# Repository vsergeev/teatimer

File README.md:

# teatimer

A simple kitchen timer implemented in digital logic on a Lattice MachXO2 CPLD.

(It's brighter in person.)

## Details

* Features
    * Large 7-segment display
    * Count-down/count-up timer
    * Alarm and silent modes
    * AAA battery powered
* Limitations
    * 10 hour battery life
* ICs
    * Lattice MachXO2-256 CPLD
    * SG-3030JC 32.768 kHz Oscillator
    * TLV61225 Boost Converter 1.5V -> 3.3V
* Dimensions of 80mm x 49mm
* Power consumption of ~100mA @ 1.5V (mostly from LEDs)

## Project Structure

* [`README.md`](README.md) - this README
* [`teatimer.v`](teatimer.v) - Verilog source
* [`teatimer_tb.v`](teatimer_tb.v) - Verilog test bench
* [`Makefile`](Makefile) - Makefile for simulation
* [`hw/`](hw/) - Schematic and layout
    * `teatimer.sch` - Eagle schematic
    * `teatimer.brd` - Eagle layout
    * [`teatimer-sch.png`](hw/teatimer-sch.png) - Schematic image
    * [`teatimer-brd.png`](hw/teatimer-brd.png) - Layout image
    * [`gerbers/`](hw/gerbers/) - Gerbers
* [`diamond/`](diamond/) - Lattice Diamond project
    * `teatimer.ldf` - Project file
    * `teatimer.v` - Symlinked Verilog source
    * [`teatimer.lpf`](diamond/teatimer.lpf) - Constraints
    * [`teatimer.jed`](diamond/teatimer.jed) - JEDEC bitstream
* [`misc/`](misc/) - Miscellaneous scripts

## Design Summary

The design uses 67 bits of state, 91% of the LUTs for logic, and all of the
I/O.

```
Number of registers:     67 out of   322 (21%)
   PFU registers:           63 out of   256 (25%)
   PIO registers:            4 out of    66 (6%)
Number of SLICEs:       117 out of   128 (91%)
   SLICEs as Logic/ROM:    117 out of   128 (91%)
   SLICEs as RAM:            0 out of    96 (0%)
   SLICEs as Carry:         27 out of   128 (21%)
Number of LUT4s:        232 out of   256 (91%)
   Number used as logic LUTs:        178
   Number used as distributed RAM:     0
   Number used as ripple logic:       54
   Number used as shift registers:     0
Number of PIO sites used: 18 + 4(JTAG) out of 22 (100%)
Number of block RAMs:  0 out of 0
Number of GSRs:  1 out of 1 (100%)
```

## Datasheets

* U1, Lattice MachXO2 CPLD, LCMXO2-256HC-4SG32C - [family datasheet](http://www.latticesemi.com/~/media/LatticeSemi/Documents/DataSheets/MachXO23/MachXO2FamilyDataSheet.pdf)
* U2, 32.768 kHz Oscillator, SG-3030JC32.7680KB:ROHS - [datasheet](https://support.epson.biz/td/api/doc_check.php?dl=brief_SG-3040JC)
* U3, Boost Converter, TLV61225DCKR - [datasheet](http://www.ti.com/lit/ds/symlink/tlv61225.pdf)
* DISP1, 7-segment Display, HDSP-B03E - [datasheet](https://docs.broadcom.com/docs/AV02-0568EN)
* SP1, 4kHz Buzzer, PKM13EPYH4000-A0 - [datasheet](http://search.murata.co.jp/Ceramy/image/img/w_hinm/S0040E.pdf)

## Schematic

## Layout

## Bill of Materials

| Qty | Part                      | Refdes             | Digi-key Part Number       | Total Price |
|:----|:--------------------------|:-------------------|:---------------------------|:------------|
| 1   | Lattice MachXO2-256 CPLD  | U1                 | 220-2636-ND                | 2.830       |
| 1   | Oscillator 32.768kHz      | U2                 | SG-3030JC32.7680KB:ROHS-ND | 1.398       |
| 1   | TLV61225 Boost Converter  | U3                 | 296-36756-1-ND             | 0.775       |
| 1   | NPN BJT (Buzzer Driver)   | Q1                 | BC817-40LT1GOSCT-ND        | 0.103       |
| 1   | PMOS FET (Polarity Prot.) | Q2                 | SI2365EDS-T1-GE3CT-ND      | 0.297       |
| 4   | Tactile Switch (Buttons)  | SW1-SW4            | CKN9085CT-ND               | 0.776       |
| 1   | Slide Switch (Power)      | SW5                | CKN9558-ND                 | 0.648       |
| 1   | 7-segment LED Display     | DISP1              | 516-2745-ND                | 2.821       |
| 1   | Buzzer 4kHz               | SP1                | 490-4698-ND                | 0.499       |
| 1   | Battery Connector AAA     | J1                 | 36-2466-ND                 | 0.928       |
| 1   | SMD Header 1x6            | JP1                | 952-3235-ND                | 0.711       |
| 1   | Inductor 4.7uH            | L1                 | 1276-6213-1-ND             | 0.153       |
| 1   | Capacitor 47uF 0603       | C1                 | 311-1897-1-ND              | 0.322       |
| 2   | Capacitor 10uF 0603       | C2,C3              | 587-3258-1-ND              | 0.238       |
| 10  | Capacitor 0.1uF 0603      | C4-C13             | 1276-1005-1-ND             | 0.073       |
| 6   | Resistor 10K 0603         | R1,R3,R5,R7,R9,R19 | 311-10KGRCT-ND             | 0.033       |
| 4   | Resistor 100K 0603        | R2,R4,R6,R8        | 311-100KGRCT-ND            | 0.029       |
| 1   | Resistor 1K 0603          | R10                | 311-1.0KGRCT-ND            | 0.010       |
| 1   | Resistor 4.7K 0603        | R21                | 311-4.7KGRCT-ND            | 0.010       |
| 1   | Resistor 0.0 0603         | R20                | 311-0.0GRCT-ND             | 0.010       |
| 8   | Resistor 300 0603         | R11-R18            | 311-300GRCT-ND             | 0.044       |
| 4   | Standoffs M3 16mm Nylon   | -                  | 952-2188-ND                | 1.504       |
| 4   | Screws M3 Nylon           | -                  | 36-29341-ND                | 0.748       |
| 1   | PCB Lead-free, Shipped    | -                  | -                          | 3.240       |
|     | **Total per unit**        |                    |                            | 18.20       |

Price breaks based on quantities to build 10 units. All prices in US dollars.

## Known Issues

* Silent mode is not 100% silent (design oversight)
* Limited battery life (~10 hours)

## Hardware Change Log

* v1 - 01/30/2017
    * Initial release

## RTL Change Log

* v0.1.0 - 01/30/2017
    * Initial release

## License

teatimer is [CC-BY-4.0](https://creativecommons.org/licenses/by/4.0/) licensed. See the included [LICENSE](LICENSE) file.

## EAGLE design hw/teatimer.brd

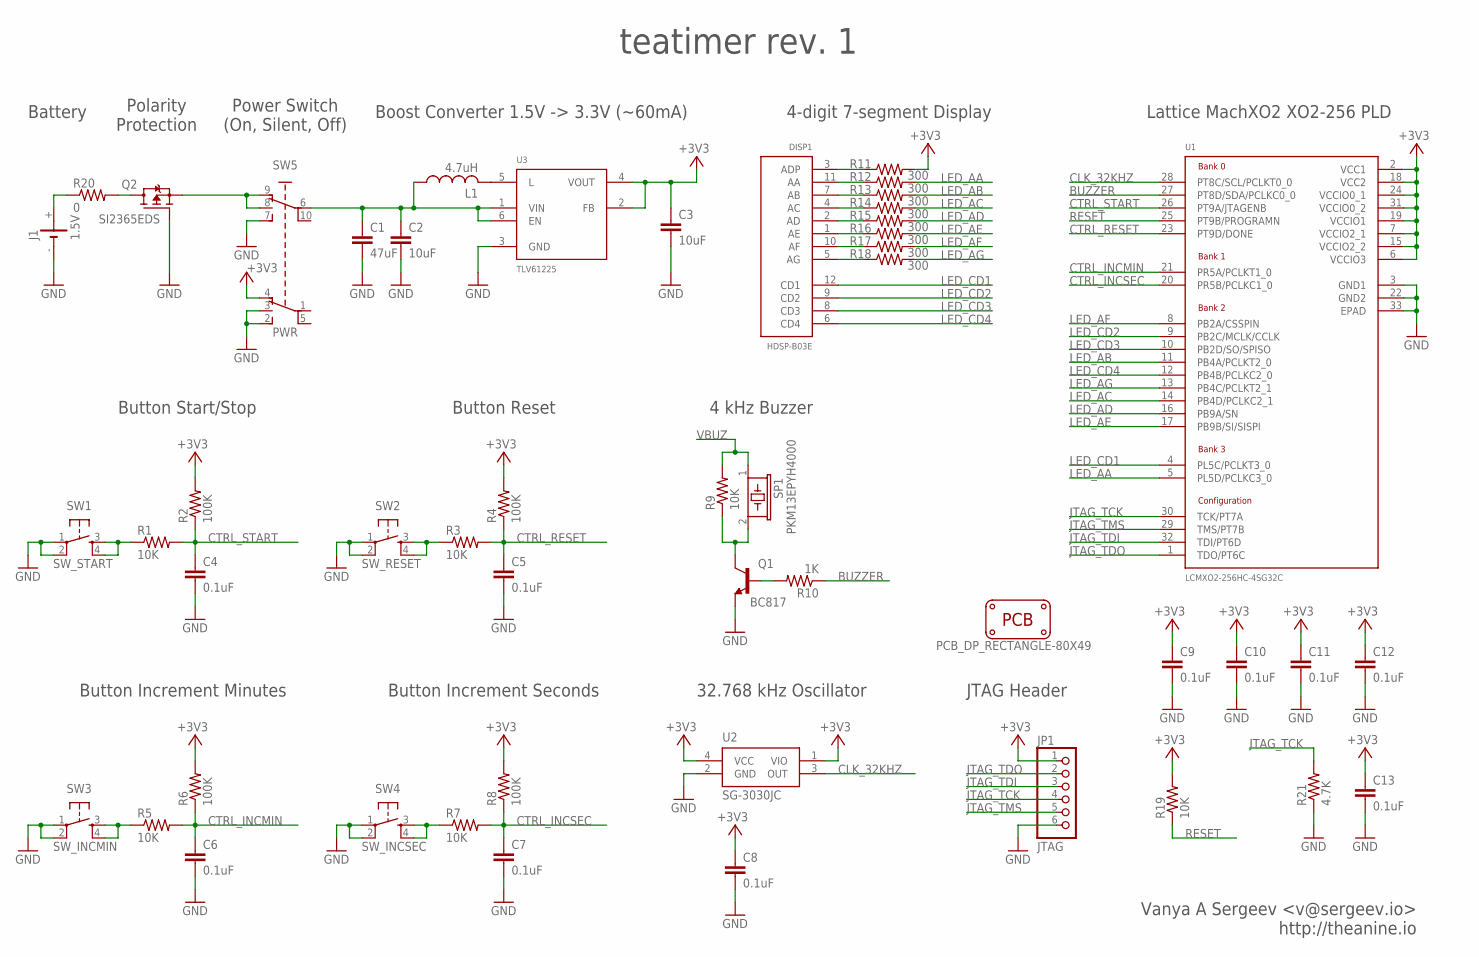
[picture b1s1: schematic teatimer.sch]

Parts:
C1: 47uF; C0805
C2, C3: 10uF; C0603
C4, C5, C6, C7, C8, C9, C10, C11, C12, C13: 0.1uF; C0603
DISP1: HDSP-B03E; HDSP-B0XE
J1: 1.5V; AAA-2466
JP1: JTAG; 1X06/90-SMD
L1: 4.7uH; L2520
PCB1: PCB_DP_RECTANGLE-80X49; DP8049_V1
Q1: BC817; SOT23-BEC
Q2: SI2365EDS; SOT23
R1, R3, R5, R7, R9, R19: 10K; R0603
R2, R4, R6, R8: 100K; R0603
R10: 1K; R0603
R11, R12, R13, R14, R15, R16, R17, R18: 300; R0603
R20: 0; R0603
R21: 4.7K; R0603
SP1: PKM13EPYH4000
SW1: SW_START; PTS645
SW2: SW_RESET; PTS645
SW3: SW_INCMIN; PTS645
SW4: SW_INCSEC; PTS645
SW5: PWR; OS203011MV9QN1
U1: LCMXO2-256HC-4SG32C; QFN32G-0.5-5X5MM
U2: SG-3030JC
U3: TLV61225; SC70-6L

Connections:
+3V3: C3.1, C8.1, C9.1, C10.1, C11.1, C12.1, C13.1, JP1.1, R2.2, R4.2, R6.2, R8.2, R11.2, R19.2, SW5.4 (B1), U1.2 (VCC1), U1.6 (VCCIO3), U1.7 (VCCIO2_1), U1.15 (VCCIO2_2), U1.18 (VCC2), U1.19 (VCCIO1), U1.24 (VCCIO0_1), U1.31 (VCCIO0_2), U2.1 (VIO), U2.4 (VCC), U3.2 (FB), U3.4 (VOUT)
BUZZER: R10.1, U1.27 (PT8D/SDA/PCLKC0_0)
CLK_32KHZ: U1.28 (PT8C/SCL/PCLKT0_0), U2.3 (OUT)
CTRL_INCMIN: C6.1, R5.2, R6.1, U1.21 (PR5A/PCLKT1_0)
CTRL_INCSEC: C7.1, R7.2, R8.1, U1.20 (PR5B/PCLKC1_0)
CTRL_RESET: C5.1, R3.2, R4.1, U1.23 (PT9D/DONE)
CTRL_START: C4.1, R1.2, R2.1, U1.26 (PT9A/JTAGENB)
GND: C1.2, C2.2, C3.2, C4.2, C5.2, C6.2, C7.2, C8.2, C9.2, C10.2, C11.2, C12.2, C13.2, J1.-, JP1.6, Q1.E, Q2.1 (G), R21.1, SW1.1, SW1.2 (P1), SW2.1, SW2.2 (P1), SW3.1, SW3.2 (P1), SW4.1, SW4.2 (P1), SW5.2 (B3), SW5.3 (B2), SW5.7 (A3), U1.3 (GND1), U1.22 (GND2), U1.33 (EPAD), U2.2 (GND), U3.3 (GND)
JTAG_TCK: JP1.4, R21.2, U1.30 (TCK/PT7A)
JTAG_TDI: JP1.3, U1.32 (TDI/PT6D)
JTAG_TDO: JP1.2, U1.1 (TDO/PT6C)
JTAG_TMS: JP1.5, U1.29 (TMS/PT7B)
LED_AA: R12.2, U1.5 (PL5D/PCLKC3_0)
LED_AB: R13.2, U1.11 (PB4A/PCLKT2_0)
LED_AC: R14.2, U1.14 (PB4D/PCLKC2_1)
LED_AD: R15.2, U1.16 (PB9A/SN)
LED_AE: R16.2, U1.17 (PB9B/SI/SISPI)
LED_AF: R17.2, U1.8 (PB2A/CSSPIN)
LED_AG: R18.2, U1.13 (PB4C/PCLKT2_1)
LED_CD1: DISP1.12 (CD1), U1.4 (PL5C/PCLKT3_0)
LED_CD2: DISP1.9 (CD2), U1.9 (PB2C/MCLK/CCLK)
LED_CD3: DISP1.8 (CD3), U1.10 (PB2D/SO/SPISO)
LED_CD4: DISP1.6 (CD4), U1.12 (PB4B/PCLKC2_0)
unnamed: Q2.2 (S), SW5.8 (A2), SW5.9 (A1)
unnamed: L1.2, U3.5 (L)
unnamed: R3.1, SW2.3 (S), SW2.4 (S1)
unnamed: R1.1, SW1.3 (S), SW1.4 (S1)
unnamed: R5.1, SW3.3 (S), SW3.4 (S1)
unnamed: R7.1, SW4.3 (S), SW4.4 (S1)
unnamed: Q1.C, R9.1, SP1.2
unnamed: Q1.B, R10.2
unnamed: DISP1.3 (ADP), R11.1
unnamed: DISP1.11 (AA), R12.1
unnamed: DISP1.7 (AB), R13.1
unnamed: DISP1.4 (AC), R14.1
unnamed: DISP1.2 (AD), R15.1
unnamed: DISP1.1 (AE), R16.1
unnamed: DISP1.10 (AF), R17.1
unnamed: DISP1.5 (AG), R18.1
unnamed: J1.+, R20.1
unnamed: Q2.3 (D), R20.2
RESET: R19.1, U1.25 (PT9B/PROGRAMN)
VBAT: C1.1, C2.1, L1.1, SW5.6 (P1), U3.1 (VIN), U3.6 (EN)
VBUZ: R9.2, SP1.1

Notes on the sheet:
Power Switch (On, Silent, Off)
Boost Converter 1.5V -> 3.3V (~60mA)
Button Start/Stop
Button Reset
Button Increment Minutes
Button Increment Seconds
32.768 kHz Oscillator
4 kHz Buzzer
4-digit 7-segment Display
Lattice MachXO2 XO2-256 PLD
JTAG Header
teatimer rev. 1
Vanya A Sergeev <v@sergeev.io> http://theanine.io
Polarity Protection
Battery

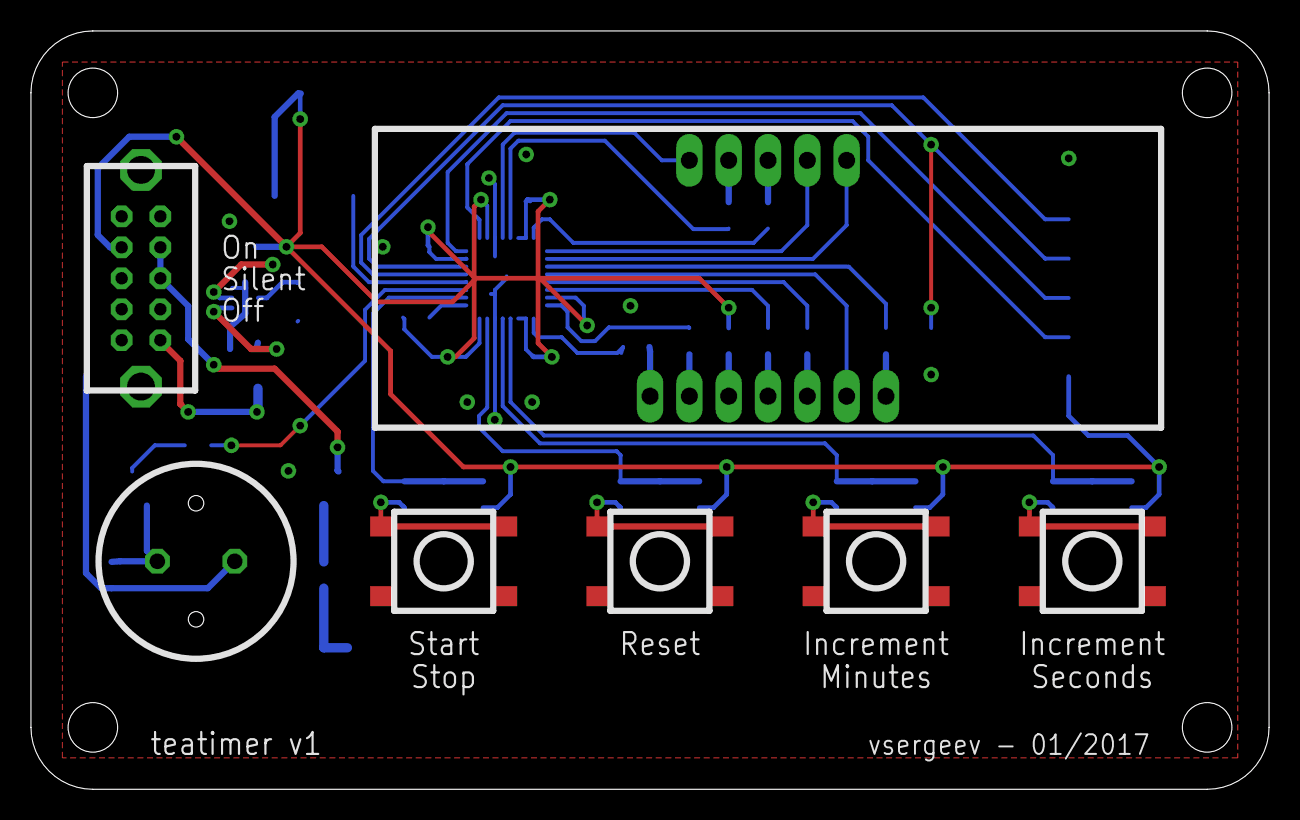
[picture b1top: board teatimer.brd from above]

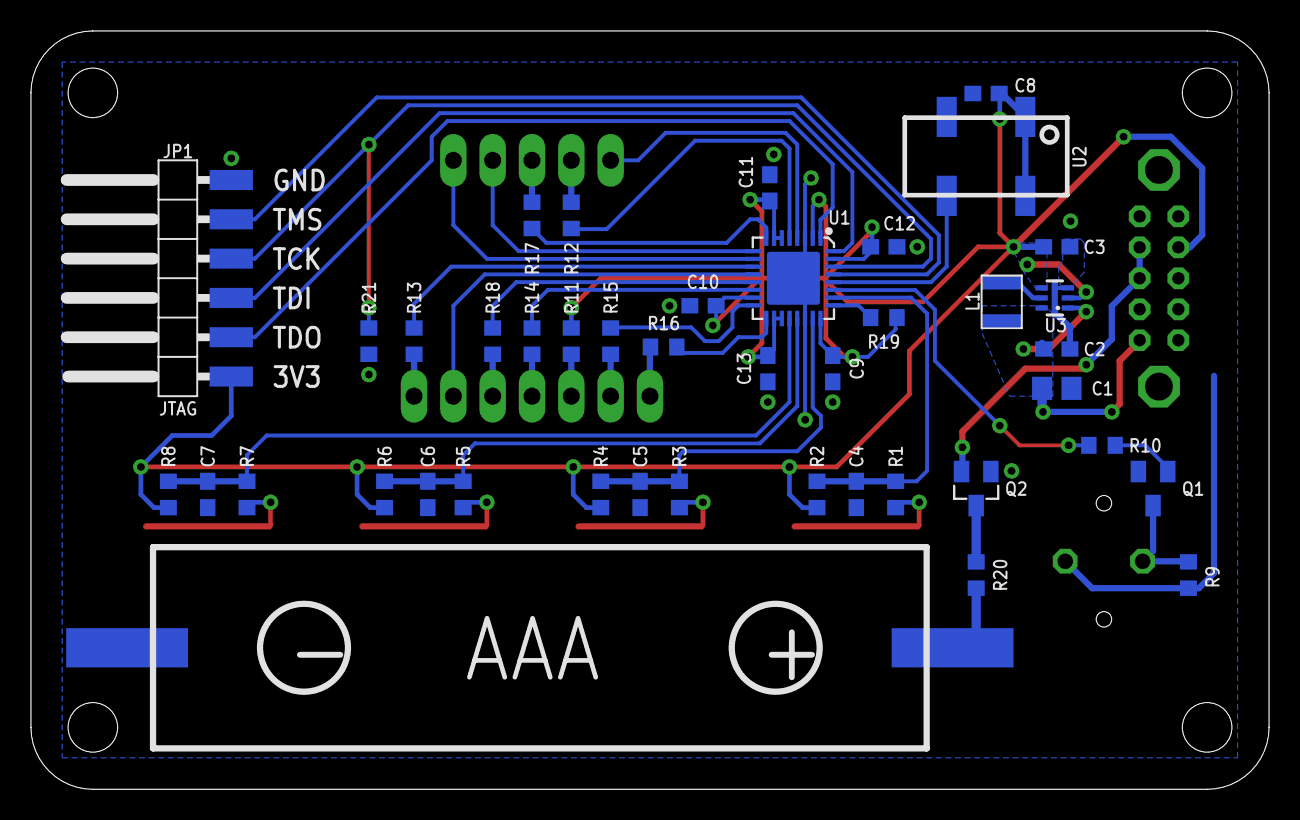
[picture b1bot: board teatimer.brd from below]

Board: 2 copper layers, 80.0 x 49.0 mm, 50 parts (42 on the bottom side), 44 nets.

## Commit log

2017-02-19 add README
2017-02-21 add photos
